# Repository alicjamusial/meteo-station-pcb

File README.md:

# METEO STATION – PCB based on ESP32 

<p align="center">
  
&nbsp; &nbsp; &nbsp;
  
</p>

### ◾ About the project

**Meteo station** is my small after-hours project that contains of **three** repositories:
- Meteo station PCB based on ESP32 (this repo)
- [Meteo station code](https://github.com/alicjamusial/meteo-station-code)
- [Meteo station 3D prints](https://github.com/alicjamusial/meteo-station-3d-print)

As the name suggest, is a DIY self-sufficient weather measuring device. I decided to design it as a PCB board with goldpins to stick-in or stick-out individual components and sensors (ESP32, BME280 etc.) to make it more reusable. It could have - of course - been integrated on board, but it would be more expensive and time-consuming to create.

As you can see - the project is designed with minimal effort 🙂 But works!

> **Warning** <br>
> This is a hobbyist project. I'm not an electronic engineer so I take no responsibility for any possible issues you may encounter :)

Gerber files for version 1.0 of Meteo Station is available [in the releases section](https://github.com/alicjamusial/meteo-station/releases/tag/release-1.0.0).

The board was designed using [KiCad](https://kicad.org/) (version: `6.0`).

I was inspired by solution created by [this guy on Instructables](https://www.instructables.com/Solar-Powered-WiFi-Weather-Station-V30/). He did a good job, so I strongly recommand exploring his meteo projects!

### ◾ Sensors & components
**Components:**
- ESP32 (ESP-WROOM-32) - main computer (with LEDs, LDO, USB-to-UART unsoldered)
- TP4056 - battery charger
- solar panel - I finally used DFRobot FIT0601 Monocrystalline Solar Panel (5V, 1A)
- 18650 battery + holder
- slide switch, LDO etc. - according to the KiCad project

**Sensors:**
- BME280 - humidity, pressure, temperature
- DS18B20 - temperature
- BH1750 - light (should be mounted on cables - outside of the box)

**Other stuff that you may need:**
- access to 3D printer to print a Stevenson cage and solar panel holder
- server (e.g. RaspberryPi) with Influx database and Grafana instance to gather data from the station and display it in a nice way

### ◾ Useful tips

- **important!** - it's a good idea to prepare your ESP32 before placing it in the station - I unsoldered all unnecessary components from it to lower the power consumption. You can see more details on [my twitter](https://twitter.com/alicja_musial/status/1494784125051584515),
- there are two possibilites to connect a solar panel to the PCB - via mini USB in the TP charger or using SC1 and SC2 connectors - depending on which solar panel you buy,
- choose the biggest solar panel you can,
- adjust timings in software to avoid complete discharge of the battery.

### ◾ Adjust it to your needs!
This is an absolutely hobbyst project :) You can use it as a reference to create something a lot better.

### ◾ License
Meteo Station PCB is available on Creative Commons Attribution Share Alike 4.0 International license (more in [license file](LICENSE.txt)). You are free to use it, modify it and produce as many of your own boards as you need.

### ◾ Final result

Cable tie and tape for the win ;)

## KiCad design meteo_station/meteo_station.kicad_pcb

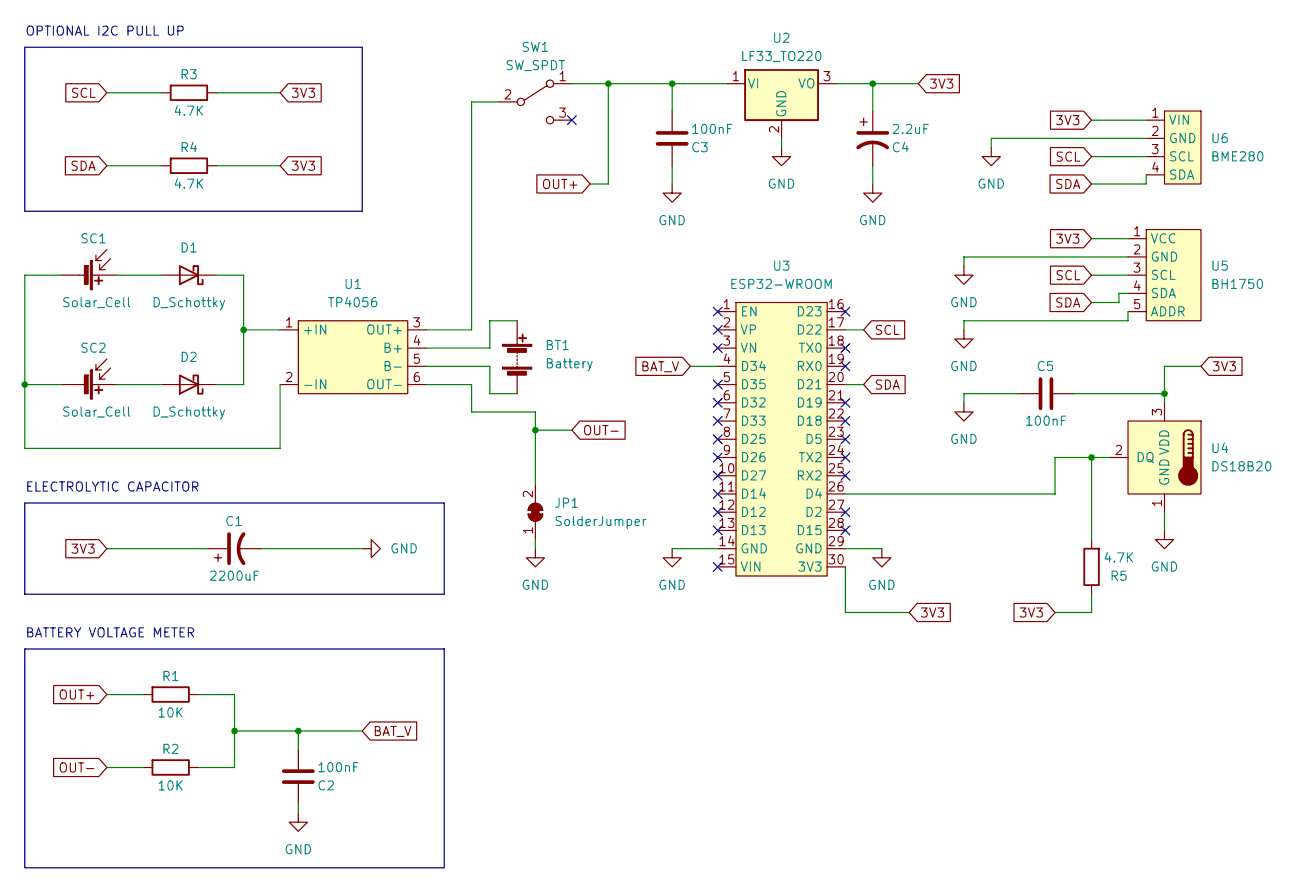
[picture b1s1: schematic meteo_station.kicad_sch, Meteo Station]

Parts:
BT1: Battery; BatteryHolder
C1: 2200uF; CP_Radial_D10.0mm_P5.00mm
C2, C3, C5: 100nF; C_0603_1608Metric
C4: 2.2uF; CP_EIA-3216-18_Kemet-A
D1, D2: D_Schottky; D_SMB
JP1: SolderJumper; SolderJumper-2_P1.3mm_Bridged_Pad1.0x1.5mm
R1, R2: 10K; R_0603_1608Metric
R3, R4, R5: 4.7K; R_0603_1608Metric
SC1, SC2: Solar_Cell; SolarPanel_JST
SW1: SW_SPDT; MTS102
U1: TP4056
U2: LF33_TO220; TO-220-3_Horizontal_TabDown
U3: ESP32-WROOM
U4: DS18B20; TO-92_Inline
U5: BH1750
U6: BME280

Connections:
3V3: C1.1, C4.1, C5.2, R3.1, R4.1, R5.1, U2.3 (VO), U3.30 (3V3), U4.3 (VDD), U5.1 (VCC), U6.1 (VIN)
BAT_V: C2.1, R1.1, R2.1, U3.4 (D34)
GND: C1.2, C2.2, C3.2, C4.2, C5.1, JP1.1 (A), U2.2 (GND), U3.14 (GND), U3.29 (GND), U4.1 (GND), U5.2 (GND), U5.5 (ADDR), U6.2 (GND)
unnamed: BT1.1 (+), U1.4 (B+)
unnamed: BT1.2 (-), U1.5 (B-)
unnamed: D1.1 (K), D2.1 (K), U1.1 (+IN)
unnamed: D1.2 (A), SC1.1 (+)
unnamed: D2.2 (A), SC2.1 (+)
unnamed: R5.2, U3.26 (D4), U4.2 (DQ)
unnamed: SC1.2 (-), SC2.2 (-), U1.2 (-IN)
unnamed: SW1.2 (B), U1.3 (OUT+)
OUT+: C3.1, R1.2, SW1.1 (A), U2.1 (VI)
OUT-: JP1.2 (B), R2.2, U1.6 (OUT-)
SCL: R3.2, U3.17 (D22), U5.3 (SCL), U6.3 (SCL)
SDA: R4.2, U3.20 (D21), U5.4 (SDA), U6.4 (SDA)

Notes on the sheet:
OPTIONAL I2C PULL UP
ELECTROLYTIC CAPACITOR
BATTERY VOLTAGE METER

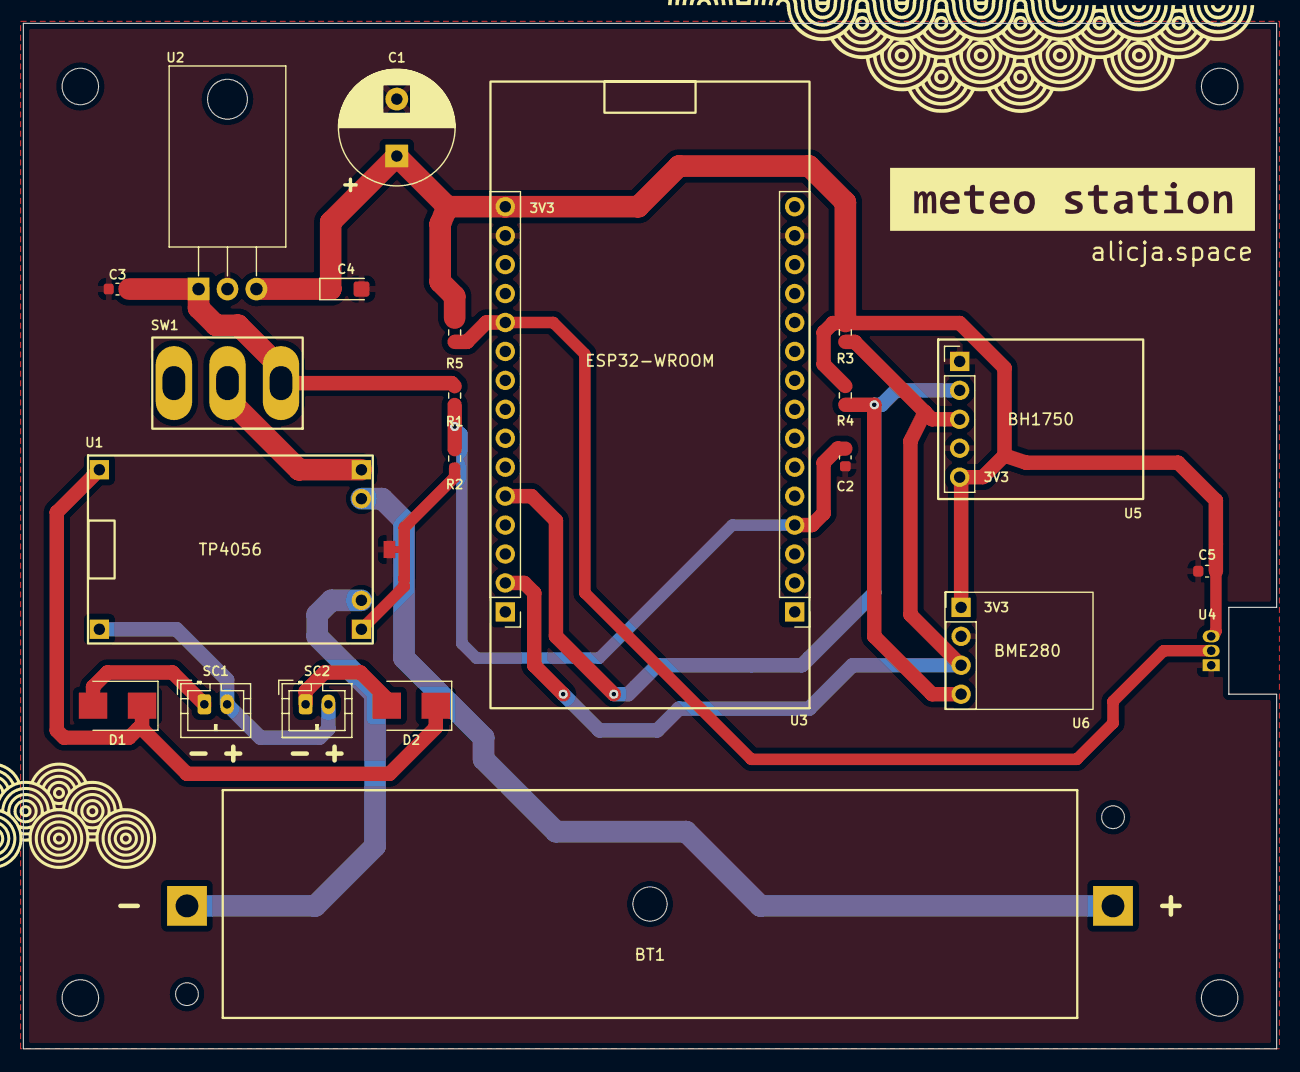
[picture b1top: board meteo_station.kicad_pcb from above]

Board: 2 copper layers, 110.0 x 90.0 mm, 23 parts (0 on the bottom side), 15 nets.

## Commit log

2022-01-24 Repo init
2022-01-24 Net fixes
2022-01-24 Fixes
2022-01-24 First random assignment
2022-01-24 First draft of PCB
2022-01-25 Add some footprints
2022-01-25 Preliminary design
2022-01-25 Add some routes
2022-01-25 Add LDO and battery voltage meter
2022-01-29 Fix some footprints
2022-01-29 Add second solar panel
2022-01-29 Update termometer footprint
2022-01-29 PCB adjustments
2022-01-29 PCB v2
2022-02-13 Change rotation to make USBs visible
2022-02-13 Add some routing
2022-02-13 Start working on logo
2022-02-13 Logo
2022-02-16 Add jumper & version
2022-02-16 Add images
2022-02-19 Add supercapacitor and 100nF
2022-02-19 Finished moving
2022-02-19 new tracks
2022-02-19 Very thick routes
2022-02-19 Typo & label
2022-09-01 Add Readme and clean the repo
2022-09-01 Readme
2022-09-18 Adjust readme
2022-09-18 Readme fixes
2022-09-18 Add info about two possibilities for connecting solar panels
2022-09-18 Typo
